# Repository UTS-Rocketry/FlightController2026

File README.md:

# ODIN - UTS Rocketry – Flight Controller 2026

## Version 1.0 - First Flight Test Release

Primary avionics flight controller for the 2026 AURC rocket.

ODIN is a 3.3V STM32-based embedded flight controller designed to manage flight-state detection, onboard sensor acquisition, telemetry transmission, and flight data logging. This release represents the first hardware-and-firmware test release for an upcoming flight test.

The current firmware is intentionally simple and robust. It runs on a superloop architecture without DMA and uses a watchdog for fault recovery. The system has been tested using hardware-in-the-loop simulated flight data and has operated reliably during testing.

---

## System Overview

### Microcontroller

* STM32 F4-series microcontroller
* 3.3V logic domain
* SWD programming and debugging via ST-Link
* Optional USB device support planned for future debug and firmware workflows
* Hardware timers available for deterministic event timing
* Watchdog enabled for fault recovery

---

## Current Firmware Architecture

The first flight test firmware uses a simple superloop design.

### Current Implementation

* No RTOS
* No DMA
* Polling-based peripheral handling
* Watchdog-supervised main loop
* Deterministic flight-state logic
* Sensor sampling over shared SPI bus
* Flash-based data logging
* LoRa telemetry transmission
* Hardware-in-the-loop test data support

This architecture was selected for the first test release to reduce complexity and improve reliability during initial flight testing.

---

## Sensors

All primary sensors are currently connected on a shared SPI bus.

### Barometer

* SPI pressure sensor
* Used for altitude estimation
* Used for flight-state detection and validation
* Locally decoupled according to sensor requirements

### IMU

* SPI accelerometer and gyroscope
* Used for:

  * Boost detection
  * Apogee validation
  * Motion and orientation monitoring
* Interrupt-capable lines available for future firmware revisions

### GPS

GPS support is planned for ODIN but is not included in the current first-flight test release due to hardware issues.

Planned GPS functions include:

* Real-time position tracking
* Post-flight recovery support
* Telemetry downlink of GPS coordinates
* Position logging to onboard storage

---

## Telemetry - SX1262 LoRa

ODIN uses an SX1262-based LoRa radio for long-range telemetry transmission.

### Current Telemetry Features

* LoRa telemetry transmission enabled
* Flight-state downlink
* Sensor-derived flight data downlink
* Battery voltage downlink
* Packet scheduling is handled in the main superloop

### Planned / Future Telemetry Features

* GPS coordinate transmission
* More complete telemetry packet structure
* Configurable LoRa parameters
* Improved fault handling for radio errors

---

## Data Logging

### Current Storage

The current first flight test release uses onboard flash memory as the primary data storage medium.

Flash logging is used because the microSD card interface was dropped from the current release after wiring issues were found during testing.

### microSD Status

microSD logging was planned for this revision; however, the SD card wiring was incorrect, and the SD card interface is not used in this test release.

### Logged / Stored Parameters

The current firmware is intended to store key flight data, including:

* Timestamp or sample counter
* Raw pressure
* Calculated altitude
* IMU acceleration
* IMU gyroscope data
* Flight-state transitions
* Battery voltage
* Event flags

---

## Power Architecture

* Main system input rail
* 3.3V regulated logic rail
* ADC-based battery voltage monitoring through resistor divider
* Local decoupling at each IC
* Bulk capacitance near high-current and noise-sensitive devices
* Solid ground reference for digital logic and sensors

### Design Considerations

* All digital logic operates at 3.3V
* Shared SPI bus used for sensors and peripherals
* Short SPI traces where possible
* Source termination is considered for high-speed SPI lines
* Switching regulator noise kept away from sensitive sensor and RF sections
* Ground reference continuity is maintained across the board

---

## Programming & Debugging

### SWD Interface

SWD is the primary programming and debugging interface.

Signals:

* SWDIO
* SWCLK
* GND
* 3.3V reference
* NRST

Used for:

* Firmware flashing
* Breakpoint debugging
* Register inspection
* Fault investigation

### USB

USB support is optional and planned for future development.

Potential future uses:

* CDC virtual COM port for debug output
* DFU firmware update support
* Ground-test data streaming

---

## First Flight Test Release Notes

This release is prepared for the first ODIN flight test.

### Included

* STM32-based flight controller firmware
* Superloop firmware architecture
* Watchdog fault recovery
* SPI sensor acquisition
* Barometer-based altitude estimation
* IMU data acquisition
* LoRa telemetry transmission
* Flash-based data logging
* Battery voltage monitoring
* Hardware-in-the-loop simulated flight data testing

### Not Included in This Release

* GPS support
* microSD card logging
* DMA-based peripheral handling
* RTOS task scheduling
* Full sensor-fusion stack
* Final telemetry packet format
* Final competition firmware architecture

### Known Issues

* The microSD card interface is not used due to incorrect wiring
* GPS is not included in this release due to hardware issues
* Firmware currently uses polling rather than DMA
* Current release prioritises reliability and simplicity over final feature completeness

---

## Core Features

* Sensor initialisation and health checks
* Watchdog-supervised main loop
* Deterministic flight-state transitions
* Flash-based onboard data storage
* LoRa telemetry transmission
* Battery voltage monitoring
* Brownout and fault-awareness support
* Hardware-in-the-loop simulation data testing

---

## Development Roadmap

Future firmware and hardware revisions are expected to include:

* GPS integration
* Corrected microSD card interface
* Improved onboard logging backend
* DMA support for selected peripherals
* More complete sensor fusion
* Refined telemetry packet scheduling
* Expanded fault detection and recovery
* USB debug and DFU support
* Full competition-ready flight software

---

## Contributors
* Michael Basangan: Software Lead
* Aditya Sriram: Advisor

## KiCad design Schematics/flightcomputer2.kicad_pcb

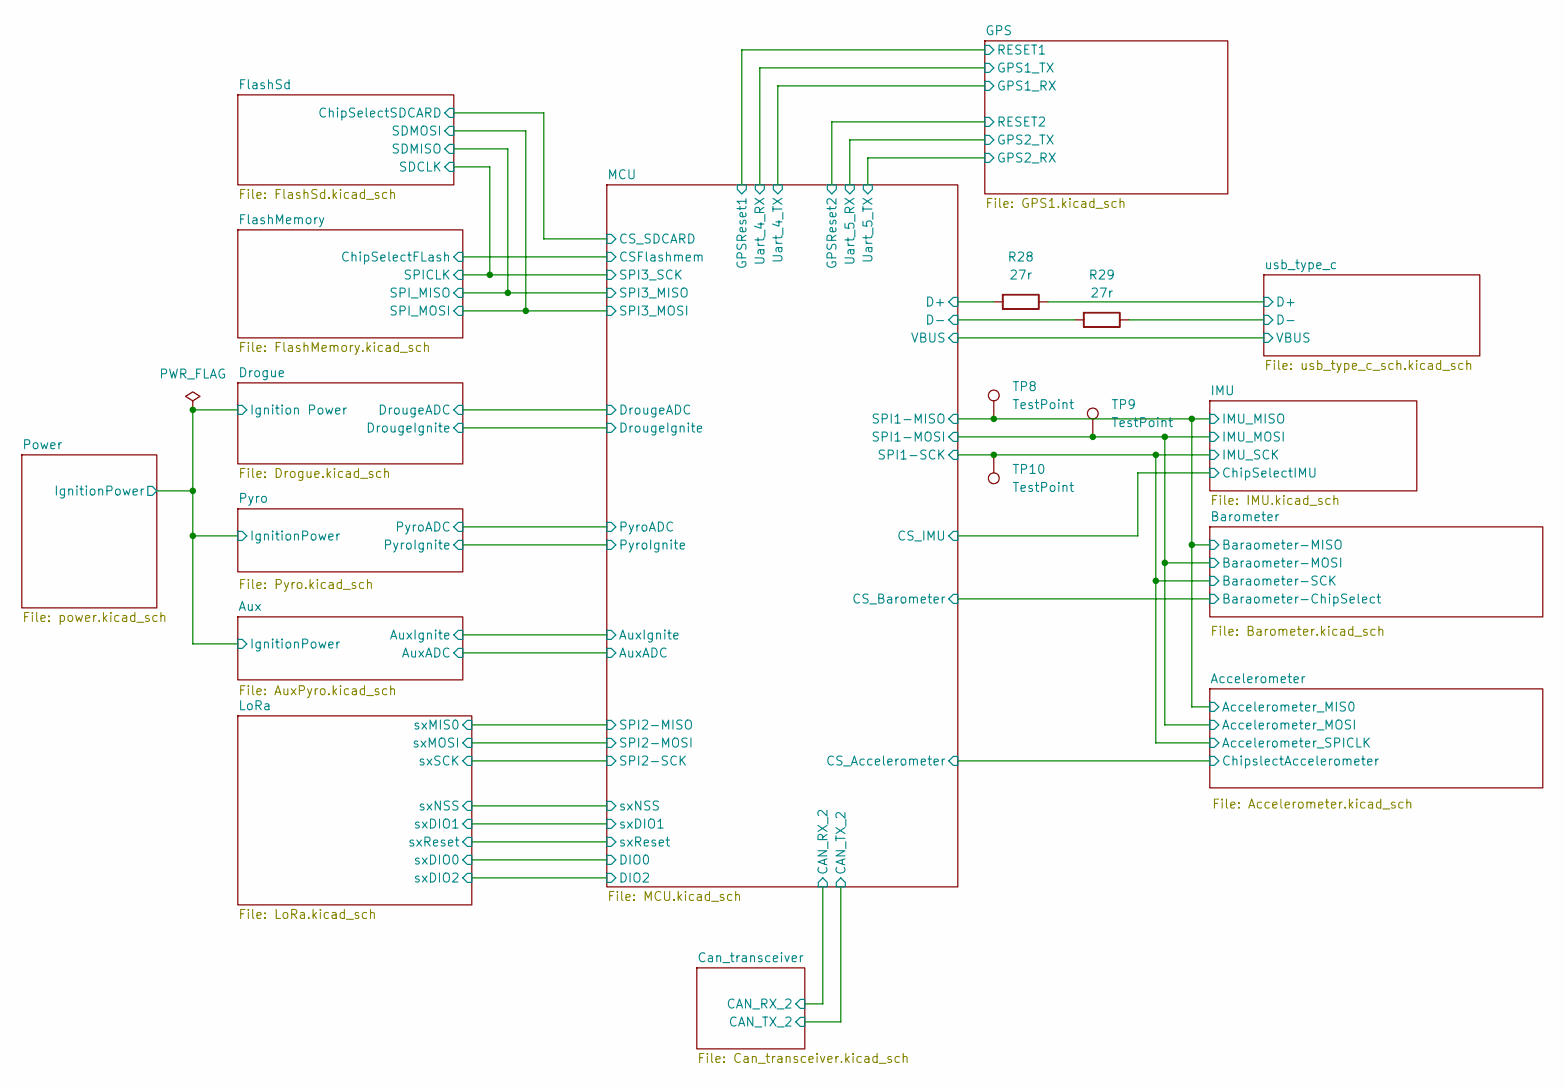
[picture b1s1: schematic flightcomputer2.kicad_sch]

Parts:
R28, R29: 27r; R_0805_2012Metric_Pad1.20x1.40mm_HandSolder; LCSC C17594
TP8, TP9, TP10: TestPoint; TestPoint_Pad_1.5x1.5mm

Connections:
/Accelerometer/Accelerometer_MIS0: TP8.1 (1_1); also elsewhere on the board
/Accelerometer/Accelerometer_MOSI: TP9.1 (1_1); also elsewhere on the board
/Accelerometer/Accelerometer_SPICLK: TP10.1 (1_1); also elsewhere on the board
/MCU/D+: R28.2; also elsewhere on the board
/MCU/D-: R29.2; also elsewhere on the board
/usb_type_c/D+: R28.1; also elsewhere on the board
/usb_type_c/D-: R29.1; also elsewhere on the board

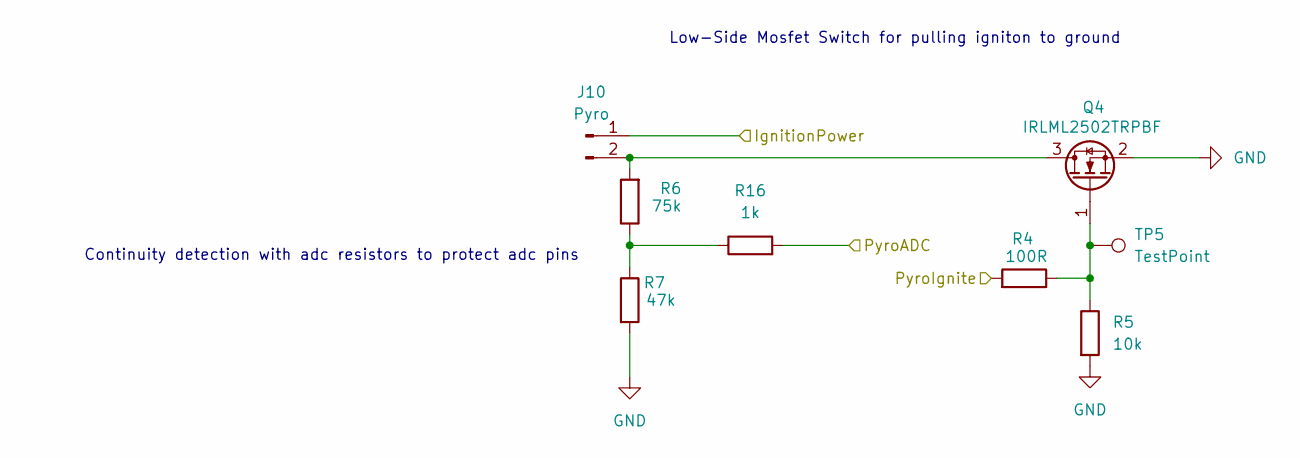
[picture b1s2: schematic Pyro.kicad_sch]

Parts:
J10: Pyro; MOLEX_26013114; LCSC C17644051
Q4: IRLML2502TRPBF; SOT23; LCSC C2589
R4: 100R; R_0805_2012Metric_Pad1.20x1.40mm_HandSolder; LCSC C17408
R5: 10k; R_0805_2012Metric_Pad1.20x1.40mm_HandSolder; LCSC C17414
R6: 75k; R_0805_2012Metric_Pad1.20x1.40mm_HandSolder; LCSC C17819
R7: 47k; R_0805_2012Metric_Pad1.20x1.40mm_HandSolder; LCSC C17713
R16: 1k; R_0805_2012Metric_Pad1.20x1.40mm_HandSolder; LCSC C17513
TP5: TestPoint; TestPoint_Pad_1.5x1.5mm

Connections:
/Aux/IgnitionPower: J10.1; also elsewhere on the board
/MCU/PyroADC: R16.2; also elsewhere on the board
/MCU/PyroIgnite: R4.2; also elsewhere on the board
GND: Q4.2 (S), R5.2, R7.2; also elsewhere on the board
unnamed: J10.2, Q4.3 (D), R6.2
unnamed: Q4.1 (G), R4.1, R5.1, TP5.1 (1_1)
unnamed: R6.1, R7.1, R16.1

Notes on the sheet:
Low-Side Mosfet Switch for pulling igniton to ground
Continuity detection with adc resistors to protect adc pins

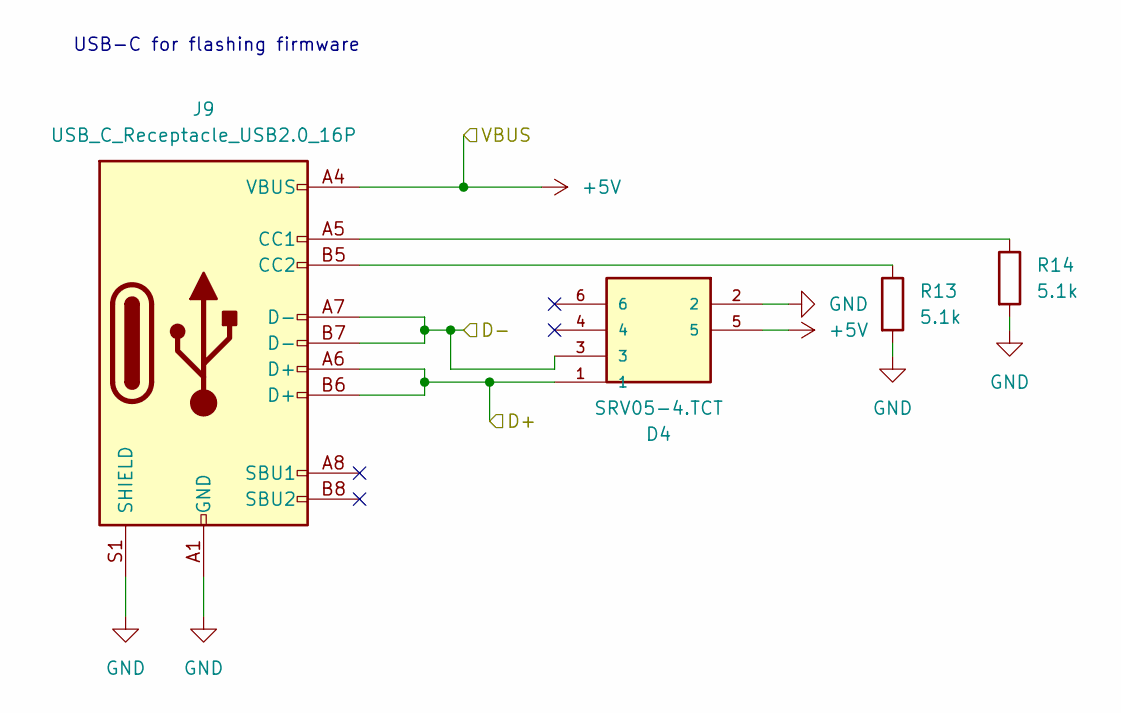
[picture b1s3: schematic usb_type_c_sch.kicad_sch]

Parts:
D4: SRV05-4.TCT; SOT95P280X145-6N; MANUFACTURER_PART_NUMBER SRV05-4.TCT; LCSC C13612
J9: USB_C_Receptacle_USB2.0_16P; USB_C_Receptacle_HRO_TYPE-C-31-M-12; LCSC C165948
R13, R14: 5.1k; R_0805_2012Metric_Pad1.20x1.40mm_HandSolder; LCSC C27834

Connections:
+5V: D4.5, J9.A4 (VBUS), J9.A9 (VBUS), J9.B4 (VBUS), J9.B9 (VBUS); also elsewhere on the board
/usb_type_c/D+: D4.1, J9.A6 (D+), J9.B6 (D+); also elsewhere on the board
/usb_type_c/D-: D4.3, J9.A7 (D-), J9.B7 (D-); also elsewhere on the board
GND: D4.2, J9.A1 (GND), J9.A12 (GND), J9.B1 (GND), J9.B12 (GND), J9.S1 (SHIELD), R13.2, R14.2; also elsewhere on the board
unnamed: J9.A5 (CC1), R14.1
unnamed: J9.B5 (CC2), R13.1

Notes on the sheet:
USB-C for flashing firmware

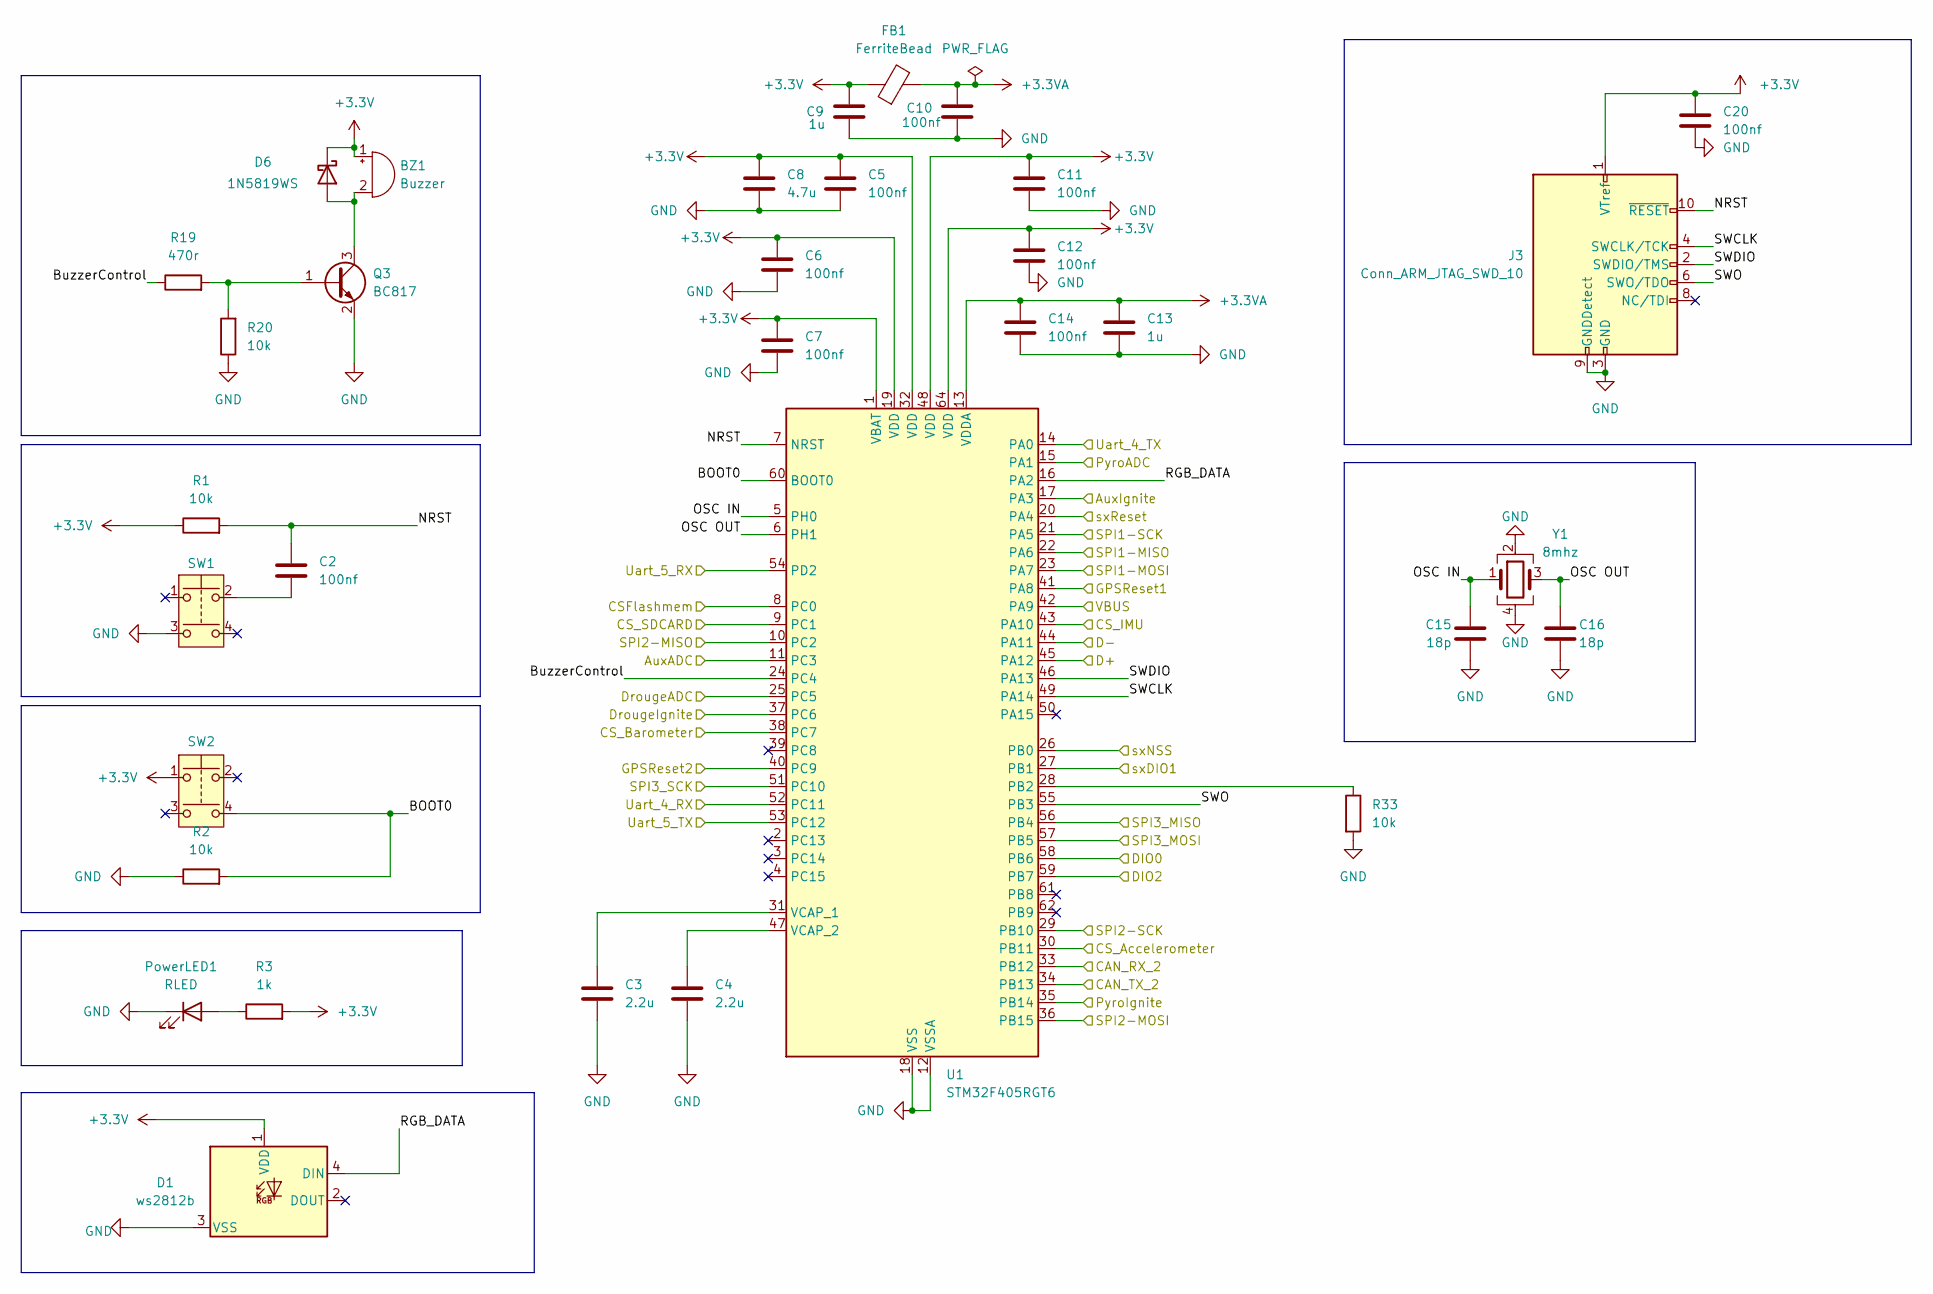
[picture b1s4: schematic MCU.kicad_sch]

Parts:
BZ1: Buzzer; Buzzer_12x9.5RM7.6; LCSC C96093
C2, C5, C6, C7, C10, C11, C12, C14, C20: 100nf; C_0805_2012Metric_Pad1.18x1.45mm_HandSolder; LCSC C49678
C3, C4: 2.2u; C_0805_2012Metric_Pad1.18x1.45mm_HandSolder; LCSC C377773
C8: 4.7u; C_0805_2012Metric_Pad1.18x1.45mm_HandSolder; LCSC C1779
C9, C13: 1u; C_0805_2012Metric_Pad1.18x1.45mm_HandSolder; LCSC C28323
C15, C16: 18p; C_0805_2012Metric_Pad1.18x1.45mm_HandSolder; LCSC C113825
D1: ws2812b; LED_WS2812B_PLCC4_5.0x5.0mm_P3.2mm; LCSC C2761795
D6: 1N5819WS; D_SOD-323; LCSC C191023
FB1: FerriteBead; R_0805_2012Metric_Pad1.20x1.40mm_HandSolder; LCSC C1015
J3: Conn_ARM_JTAG_SWD_10; PinHeader_2x05_P1.27mm_Vertical; LCSC C22438120
PowerLED1: RLED; LED_0603_1608Metric_Pad1.05x0.95mm_HandSolder; LCSC C965799
Q3: BC817; SOT-23; LCSC C39828
R1, R2, R20: 10k; R_0805_2012Metric_Pad1.20x1.40mm_HandSolder; LCSC C17414
R3: 1k; R_0805_2012Metric_Pad1.20x1.40mm_HandSolder; LCSC C17513
R19: 470r; R_0805_2012Metric_Pad1.20x1.40mm_HandSolder; LCSC C17710
R33: 10k; R_0805_2012Metric; LCSC C17414
SW1, SW2: SAMZO G4R0015010; LCSC C49393646
U1: STM32F405RGT6; LQFP-64_10x10mm_P0.5mm; LCSC C15742
Y1: 8mhz; Crystal_SMD_3225-4Pin_3.2x2.5mm_HandSoldering; LCSC C19723344

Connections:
+3.3V: BZ1.1 (+), C5.1, C6.1, C7.1, C8.1, C9.2, C11.1, C12.1, C20.1, D1.1 (VDD), D6.1 (K), FB1.1, J3.1 (VTref), R1.1, R3.2, SW2.1, U1.1 (VBAT), U1.19 (VDD), U1.32 (VDD), U1.48 (VDD), U1.64 (VDD); also elsewhere on the board
+3.3VA: C10.2, C13.1, C14.1, FB1.2, U1.13 (VDDA)
+5V: U1.42 (PA9); also elsewhere on the board
/Accelerometer/Accelerometer_MIS0: U1.22 (PA6); also elsewhere on the board
/Accelerometer/Accelerometer_MOSI: U1.23 (PA7); also elsewhere on the board
/Accelerometer/Accelerometer_SPICLK: U1.21 (PA5); also elsewhere on the board
/Accelerometer/ChipslectAccelerometer: U1.30 (PB11); also elsewhere on the board
/Aux/AuxADC: U1.11 (PC3); also elsewhere on the board
/Aux/AuxIgnite: U1.17 (PA3); also elsewhere on the board
/Barometer/Baraometer-ChipSelect: U1.38 (PC7); also elsewhere on the board
/Can_transceiver/CAN_RX_2: U1.33 (PB12); also elsewhere on the board
/Can_transceiver/CAN_TX_2: U1.34 (PB13); also elsewhere on the board
/Drogue/DrougeADC: U1.25 (PC5); also elsewhere on the board
/Drogue/DrougeIgnite: U1.37 (PC6); also elsewhere on the board
/FlashMemory/ChipSelectFLash: U1.8 (PC0); also elsewhere on the board
/FlashMemory/SPICLK: U1.51 (PC10); also elsewhere on the board
/FlashMemory/SPI_MISO: U1.56 (PB4); also elsewhere on the board
/FlashMemory/SPI_MOSI: U1.57 (PB5); also elsewhere on the board
/FlashSd/ChipSelectSDCARD: U1.9 (PC1); also elsewhere on the board
/GPS/GPS1_RX: U1.14 (PA0); also elsewhere on the board
/GPS/GPS1_TX: U1.52 (PC11); also elsewhere on the board
/GPS/GPS2_RX: U1.53 (PC12); also elsewhere on the board
/GPS/GPS2_TX: U1.54 (PD2); also elsewhere on the board
/GPS/RESET1: U1.41 (PA8); also elsewhere on the board
/GPS/RESET2: U1.40 (PC9); also elsewhere on the board
/IMU/ChipSelectIMU: U1.43 (PA10); also elsewhere on the board
/LoRa/sxDIO0: U1.58 (PB6); also elsewhere on the board
/LoRa/sxDIO1: U1.27 (PB1); also elsewhere on the board
/LoRa/sxDIO2: U1.59 (PB7); also elsewhere on the board
/LoRa/sxMIS0: U1.10 (PC2); also elsewhere on the board
/LoRa/sxMOSI: U1.36 (PB15); also elsewhere on the board
/LoRa/sxNSS: U1.26 (PB0); also elsewhere on the board
/LoRa/sxReset: U1.20 (PA4); also elsewhere on the board
/LoRa/sxSCK: U1.29 (PB10); also elsewhere on the board
/MCU/BOOT0: R2.2, SW2.4, U1.60 (BOOT0)
/MCU/BuzzerControl: R19.1, U1.24 (PC4)
/MCU/D+: U1.45 (PA12); also elsewhere on the board
/MCU/D-: U1.44 (PA11); also elsewhere on the board
/MCU/NRST: C2.1, J3.10 (~RESET), R1.2, U1.7 (NRST)
/MCU/OSC IN: C15.1, U1.5 (PH0), Y1.1
/MCU/OSC OUT: C16.1, U1.6 (PH1), Y1.3
/MCU/PyroADC: U1.15 (PA1); also elsewhere on the board
/MCU/PyroIgnite: U1.35 (PB14); also elsewhere on the board
/MCU/RGB_DATA: D1.4 (DIN), U1.16 (PA2)
/MCU/SWCLK: J3.4 (SWCLK/TCK), U1.49 (PA14)
/MCU/SWDIO: J3.2 (SWDIO/TMS), U1.46 (PA13)
/MCU/SWO: J3.6 (SWO/TDO), U1.55 (PB3)
GND: C3.2, C4.2, C5.2, C6.2, C7.2, C8.2, C9.1, C10.1, C11.2, C12.2, C13.2, C14.2, C15.2, C16.2, C20.2, D1.3 (VSS), J3.3 (GND), J3.5 (GND), J3.9 (GNDDetect), PowerLED1.1 (K), Q3.2 (E), R2.1, R20.1, R33.2, SW1.3, U1.12 (VSSA), U1.18 (VSS), U1.63 (VSS), Y1.2, Y1.4; also elsewhere on the board
unnamed: BZ1.2 (-), D6.2 (A), Q3.3 (C)
unnamed: C2.2, SW1.2
unnamed: PowerLED1.2 (A), R3.1
unnamed: Q3.1 (B), R19.2, R20.2
unnamed: R33.1, U1.28 (PB2)
unnamed: C3.1, U1.31 (VCAP_1)
unnamed: C4.1, U1.47 (VCAP_2)

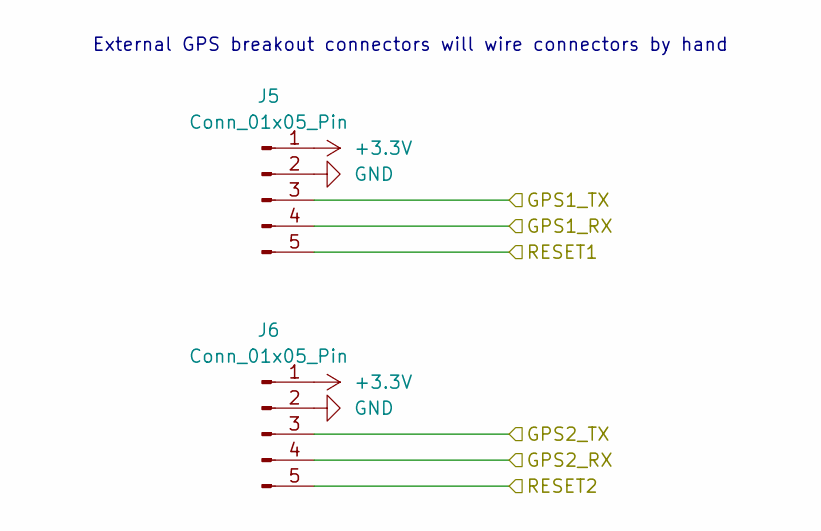
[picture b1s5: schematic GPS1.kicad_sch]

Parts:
J5, J6: Conn_01x05_Pin; JST_B5B-XH-A; LCSC C157991

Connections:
+3.3V: J5.1, J6.1; also elsewhere on the board
/GPS/GPS1_RX: J5.4; also elsewhere on the board
/GPS/GPS1_TX: J5.3; also elsewhere on the board
/GPS/GPS2_RX: J6.4; also elsewhere on the board
/GPS/GPS2_TX: J6.3; also elsewhere on the board
/GPS/RESET1: J5.5; also elsewhere on the board
/GPS/RESET2: J6.5; also elsewhere on the board
GND: J5.2, J6.2; also elsewhere on the board

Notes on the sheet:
External GPS breakout connectors will wire connectors by hand

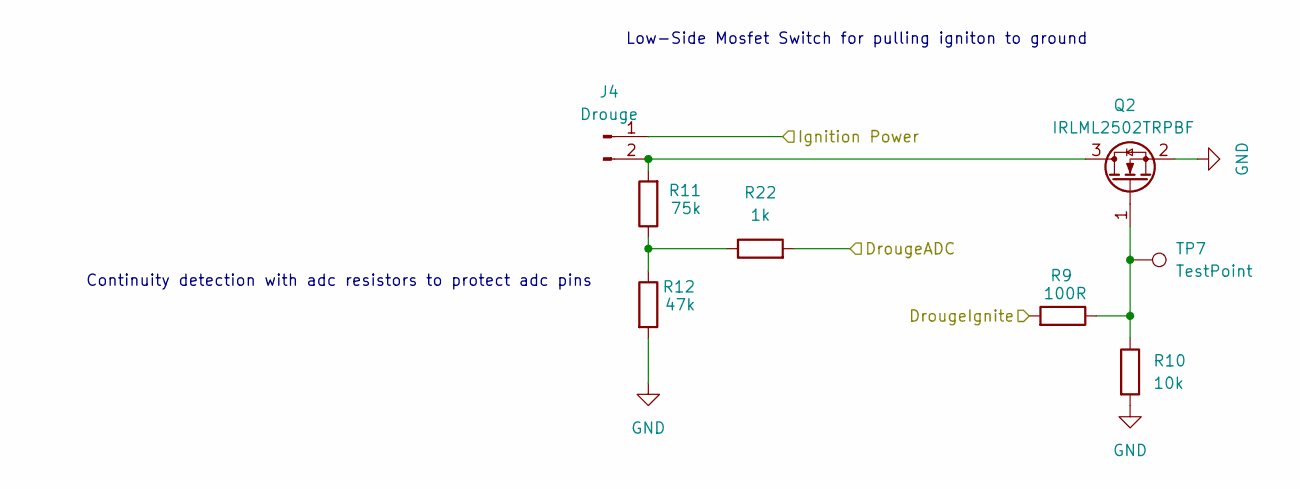
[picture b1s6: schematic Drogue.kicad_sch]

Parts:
J4: Drouge; MOLEX_26013114; LCSC C17644051
Q2: IRLML2502TRPBF; SOT23; LCSC C2589
R9: 100R; R_0805_2012Metric_Pad1.20x1.40mm_HandSolder; LCSC C17408
R10: 10k; R_0805_2012Metric_Pad1.20x1.40mm_HandSolder; LCSC C17414
R11: 75k; R_0805_2012Metric_Pad1.20x1.40mm_HandSolder; LCSC C17819
R12: 47k; R_0805_2012Metric_Pad1.20x1.40mm_HandSolder; LCSC C17713
R22: 1k; R_0805_2012Metric_Pad1.20x1.40mm_HandSolder; LCSC C17513
TP7: TestPoint; TestPoint_Pad_1.5x1.5mm

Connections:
/Aux/IgnitionPower: J4.1; also elsewhere on the board
/Drogue/DrougeADC: R22.2; also elsewhere on the board
/Drogue/DrougeIgnite: R9.2; also elsewhere on the board
GND: Q2.2 (S), R10.2, R12.2; also elsewhere on the board
unnamed: J4.2, Q2.3 (D), R11.2
unnamed: Q2.1 (G), R9.1, R10.1, TP7.1 (1_1)
unnamed: R11.1, R12.1, R22.1

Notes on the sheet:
Continuity detection with adc resistors to protect adc pins
Low-Side Mosfet Switch for pulling igniton to ground

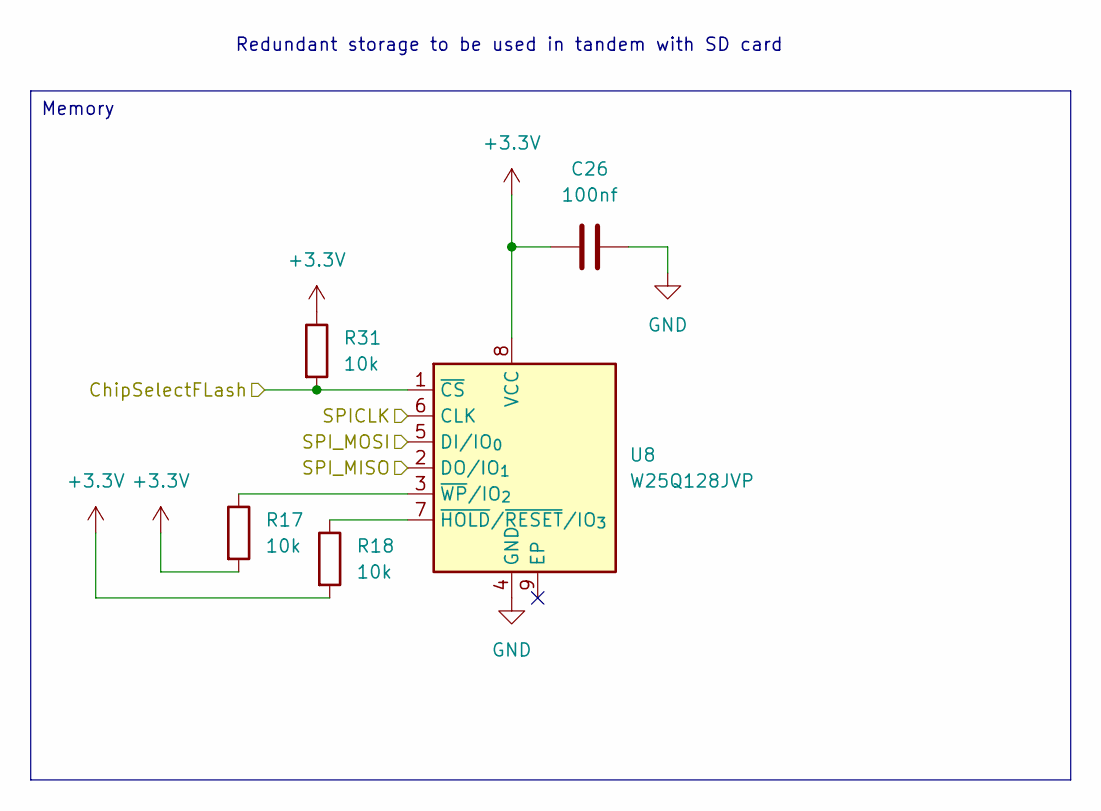
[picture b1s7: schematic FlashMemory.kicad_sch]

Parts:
C26: 100nf; C_0805_2012Metric_Pad1.18x1.45mm_HandSolder; LCSC C49678
R17, R18, R31: 10k; R_0805_2012Metric_Pad1.20x1.40mm_HandSolder; LCSC C17414
U8: W25Q128JVP; WSON-8-1EP_6x5mm_P1.27mm_EP3.4x4.3mm; LCSC C190862

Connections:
+3.3V: C26.1, R17.2, R18.2, R31.1, U8.8 (VCC); also elsewhere on the board
/FlashMemory/ChipSelectFLash: R31.2, U8.1 (~CS); also elsewhere on the board
/FlashMemory/SPICLK: U8.6 (CLK); also elsewhere on the board
/FlashMemory/SPI_MISO: U8.2 (DO/IO_{1}); also elsewhere on the board
/FlashMemory/SPI_MOSI: U8.5 (DI/IO_{0}); also elsewhere on the board
GND: C26.2, U8.4 (GND); also elsewhere on the board
unnamed: R18.1, U8.7 (~HOLD/~RESET/IO_{3})
unnamed: R17.1, U8.3 (~WP/IO_{2})

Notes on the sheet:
Redundant storage to be used in tandem with SD card
Memory

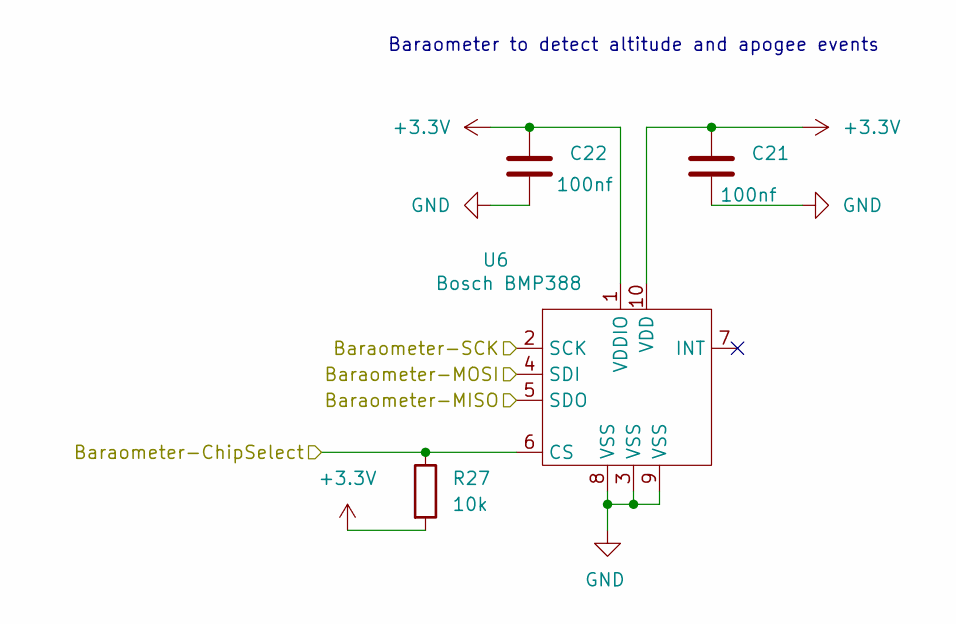
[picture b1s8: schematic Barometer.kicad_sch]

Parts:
C21, C22: 100nf; C_0805_2012Metric_Pad1.18x1.45mm_HandSolder; LCSC C49678
R27: 10k; R_0805_2012Metric_Pad1.20x1.40mm_HandSolder; LCSC C17414
U6: Bosch BMP388; PQFN50P200X200X80-10N; LCSC C779278

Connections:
+3.3V: C21.1, C22.1, R27.2, U6.1 (VDDIO), U6.10 (VDD); also elsewhere on the board
/Accelerometer/Accelerometer_MIS0: U6.5 (SDO); also elsewhere on the board
/Accelerometer/Accelerometer_MOSI: U6.4 (SDI); also elsewhere on the board
/Accelerometer/Accelerometer_SPICLK: U6.2 (SCK); also elsewhere on the board
/Barometer/Baraometer-ChipSelect: R27.1, U6.6 (CS); also elsewhere on the board
GND: C21.2, C22.2, U6.3 (VSS), U6.8 (VSS), U6.9 (VSS); also elsewhere on the board

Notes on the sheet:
Baraometer to detect altitude and apogee events

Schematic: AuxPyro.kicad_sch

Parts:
J2: Pyro; MOLEX_26013114; LCSC C17644051
Q1: IRLML2502TRPBF; SOT23; LCSC C2589
R21: 1k; R_0805_2012Metric_Pad1.20x1.40mm_HandSolder; LCSC C17513
R23: 100R; R_0805_2012Metric_Pad1.20x1.40mm_HandSolder; LCSC C17408
R24: 10k; R_0805_2012Metric_Pad1.20x1.40mm_HandSolder; LCSC C17414
R25: 75k; R_0805_2012Metric_Pad1.20x1.40mm_HandSolder; LCSC C17819
R26: 47k; R_0805_2012Metric_Pad1.20x1.40mm_HandSolder; LCSC C17713
TP6: TestPoint; TestPoint_Pad_1.5x1.5mm

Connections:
/Aux/AuxADC: R21.2; also elsewhere on the board
/Aux/AuxIgnite: R23.2; also elsewhere on the board
/Aux/IgnitionPower: J2.1; also elsewhere on the board
GND: Q1.2 (S), R24.2, R26.2; also elsewhere on the board
unnamed: J2.2, Q1.3 (D), R25.2
unnamed: Q1.1 (G), R23.1, R24.1, TP6.1 (1_1)
unnamed: R21.1, R25.1, R26.1

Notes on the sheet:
Continuity detection with adc resistors to protect adc pins
Low-Side Mosfet Switch for pulling igniton to ground

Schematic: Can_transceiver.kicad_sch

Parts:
C17: 100nf; C_0805_2012Metric_Pad1.18x1.45mm_HandSolder; LCSC C49678
CAN_IN1: CAN; MOLEX_26013114; LCSC C17644051
CAN_OUT1: CAN; MOLEX_26013114; LCSC C17644051
JP1: SolderJumper_2_Open; SolderJumper-2_P1.3mm_Open_TrianglePad1.0x1.5mm; not fitted
R8: 120R; R_0805_2012Metric_Pad1.20x1.40mm_HandSolder; LCSC C17437
U2: SN65HVD230; SOIC-8_3.9x4.9mm_P1.27mm; LCSC C12084

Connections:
+3.3V: C17.1, U2.3 (VCC); also elsewhere on the board
/Can_transceiver/CANH: CAN_IN1.1, CAN_OUT1.1, R8.1, U2.7 (CANH)
/Can_transceiver/CANL: CAN_IN1.2, CAN_OUT1.2, JP1.2 (B), U2.6 (CANL)
/Can_transceiver/CAN_RX_2: U2.4 (R); also elsewhere on the board
/Can_transceiver/CAN_TX_2: U2.1 (D); also elsewhere on the board
GND: C17.2, U2.2 (GND), U2.8 (Rs); also elsewhere on the board
unnamed: JP1.1 (A), R8.2

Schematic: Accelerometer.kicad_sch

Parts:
C27: 100nf; C_0805_2012Metric_Pad1.18x1.45mm_HandSolder; LCSC C49678
C28: 1u; C_0805_2012Metric_Pad1.18x1.45mm_HandSolder; LCSC C28323
R32: 10k; R_0805_2012Metric_Pad1.20x1.40mm_HandSolder; LCSC C17414
U9: H3LIS331DL; PQFN50P300X300X100-16N; LCSC C2655074

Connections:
+3.3V: C27.2, C28.2, R32.1, U9.1 (Vdd_IO), U9.14 (VDD), U9.15 (VDD); also elsewhere on the board
/Accelerometer/Accelerometer_MIS0: U9.7 (SDO/SA0); also elsewhere on the board
/Accelerometer/Accelerometer_MOSI: U9.6 (SDA/SDI/SDO); also elsewhere on the board
/Accelerometer/Accelerometer_SPICLK: U9.4 (SCL/SPC); also elsewhere on the board
/Accelerometer/ChipslectAccelerometer: R32.2, U9.8 (CS); also elsewhere on the board
GND: C27.1, C28.1, U9.5 (GND), U9.12 (GND); also elsewhere on the board

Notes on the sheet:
High g imu for liftoff data

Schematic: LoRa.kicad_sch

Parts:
C1: 100nf; C_0805_2012Metric_Pad1.18x1.45mm_HandSolder; LCSC C49678
J7: Conn_Coaxial_Small; SMA_Amphenol_132291_Vertical; LCSC C3172376
U5: RFM95W-915S2; XCVR_RFM95W-915S2; LCSC C2844473

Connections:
+3.3V: C1.1, U5.13 (3.3V); also elsewhere on the board
/LoRa/sxDIO0: U5.14 (DIO0); also elsewhere on the board
/LoRa/sxDIO1: U5.15 (DIO1); also elsewhere on the board
/LoRa/sxDIO2: U5.16 (DIO2); also elsewhere on the board
/LoRa/sxMIS0: U5.2 (MISO); also elsewhere on the board
/LoRa/sxMOSI: U5.3 (MOSI); also elsewhere on the board
/LoRa/sxNSS: U5.5 (NSS); also elsewhere on the board
/LoRa/sxReset: U5.6 (RESET); also elsewhere on the board
/LoRa/sxSCK: U5.4 (SCK); also elsewhere on the board
GND: C1.2, J7.2 (Ext), U5.1 (GND), U5.8 (GND), U5.10 (GND); also elsewhere on the board
unnamed: J7.1 (In), U5.9 (ANT)

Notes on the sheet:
Lora module to coaxial connector

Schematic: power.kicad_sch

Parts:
C18: 100nf; C_0805_2012Metric_Pad1.18x1.45mm_HandSolder; LCSC C49678
C19: 10u; C_0805_2012Metric_Pad1.18x1.45mm_HandSolder; LCSC C15850
D2, D3: D_Schottky; D_2114_3652Metric; LCSC C113936
Q6: Q_PMOS_GSD; SOIC127P599X175-8N; LCSC C16072
R30: 47k; R_0805_2012Metric_Pad1.20x1.40mm_HandSolder; LCSC C17713
TP1, TP2, TP3: TestPoint; TestPoint_Pad_1.5x1.5mm
TP4: TestPoint; TestPoint_Pad_2.5x2.5mm
U3: PowerIn; MOLEX_26013114; LCSC C17644051
U4: LDL1117-3.3; SOT230P700X180-4N; LCSC C435835

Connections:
+3.3V: C19.1, TP3.1 (1_1), U4.2 (Vout), U4.4 (Vout); also elsewhere on the board
+5V: D3.2 (A); also elsewhere on the board
+BATT: Q6.1 (S), Q6.2 (Source), Q6.3 (Source), TP1.1 (1_1), U3.1
/Aux/IgnitionPower: D2.2 (A), Q6.5 (D), Q6.6 (Drain), Q6.7 (Drain), TP2.1 (1_1); also elsewhere on the board
GND: C18.2, C19.2, R30.2, TP4.1 (1_1), U3.2, U4.1 (GND); also elsewhere on the board
unnamed: C18.1, D2.1 (K), D3.1 (K), U4.3 (Vin)
unnamed: Q6.4 (G), R30.1

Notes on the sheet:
Flowback protection for usb and battery
The main protection point for the mosfet is the adc continuty checking pins
P-mosfet for reverse polarity protection (be advised extra pins are there just to sync with the footprint but treated as a normal p-mosfet)
Power in connector

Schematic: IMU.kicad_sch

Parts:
C24, C25: 100nf; C_0805_2012Metric_Pad1.18x1.45mm_HandSolder; LCSC C49678
R36: 10k; R_0805_2012Metric_Pad1.20x1.40mm_HandSolder; LCSC C17414
U7: LSM6DS3TR-C; LGA-14-2.5X3MM; LCSC C2655100

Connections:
+3.3V: C24.1, C25.1, R36.1, U7.2 (SDx), U7.3 (SCx), U7.5 (VDDIO), U7.8 (VDD); also elsewhere on the board
/Accelerometer/Accelerometer_MIS0: U7.1 (SDO/SA0); also elsewhere on the board
/Accelerometer/Accelerometer_MOSI: U7.14 (SDA); also elsewhere on the board
/Accelerometer/Accelerometer_SPICLK: U7.13 (SCL); also elsewhere on the board
/IMU/ChipSelectIMU: R36.2, U7.12 (CS); also elsewhere on the board
GND: C24.2, C25.2, U7.6 (GND), U7.7 (GND); also elsewhere on the board

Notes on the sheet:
Imu for control systems and data logging

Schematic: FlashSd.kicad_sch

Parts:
J8: Micro_SD_Card; microSD_HC_Molex_47219-2001; LCSC C164170
R15: 10k; R_0805_2012Metric_Pad1.20x1.40mm_HandSolder; LCSC C17414

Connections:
+3.3V: J8.4 (VDD), R15.1; also elsewhere on the board
/FlashMemory/SPICLK: J8.5 (CLK); also elsewhere on the board
/FlashMemory/SPI_MISO: J8.7 (DAT0); also elsewhere on the board
/FlashMemory/SPI_MOSI: J8.3 (CMD); also elsewhere on the board
/FlashSd/ChipSelectSDCARD: J8.2 (DAT3/CD), R15.2; also elsewhere on the board
GND: J8.6 (VSS), J8.9 (SHIELD); also elsewhere on the board

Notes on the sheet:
SD Card for flight telemetry logging and possible lookup tables for control systems

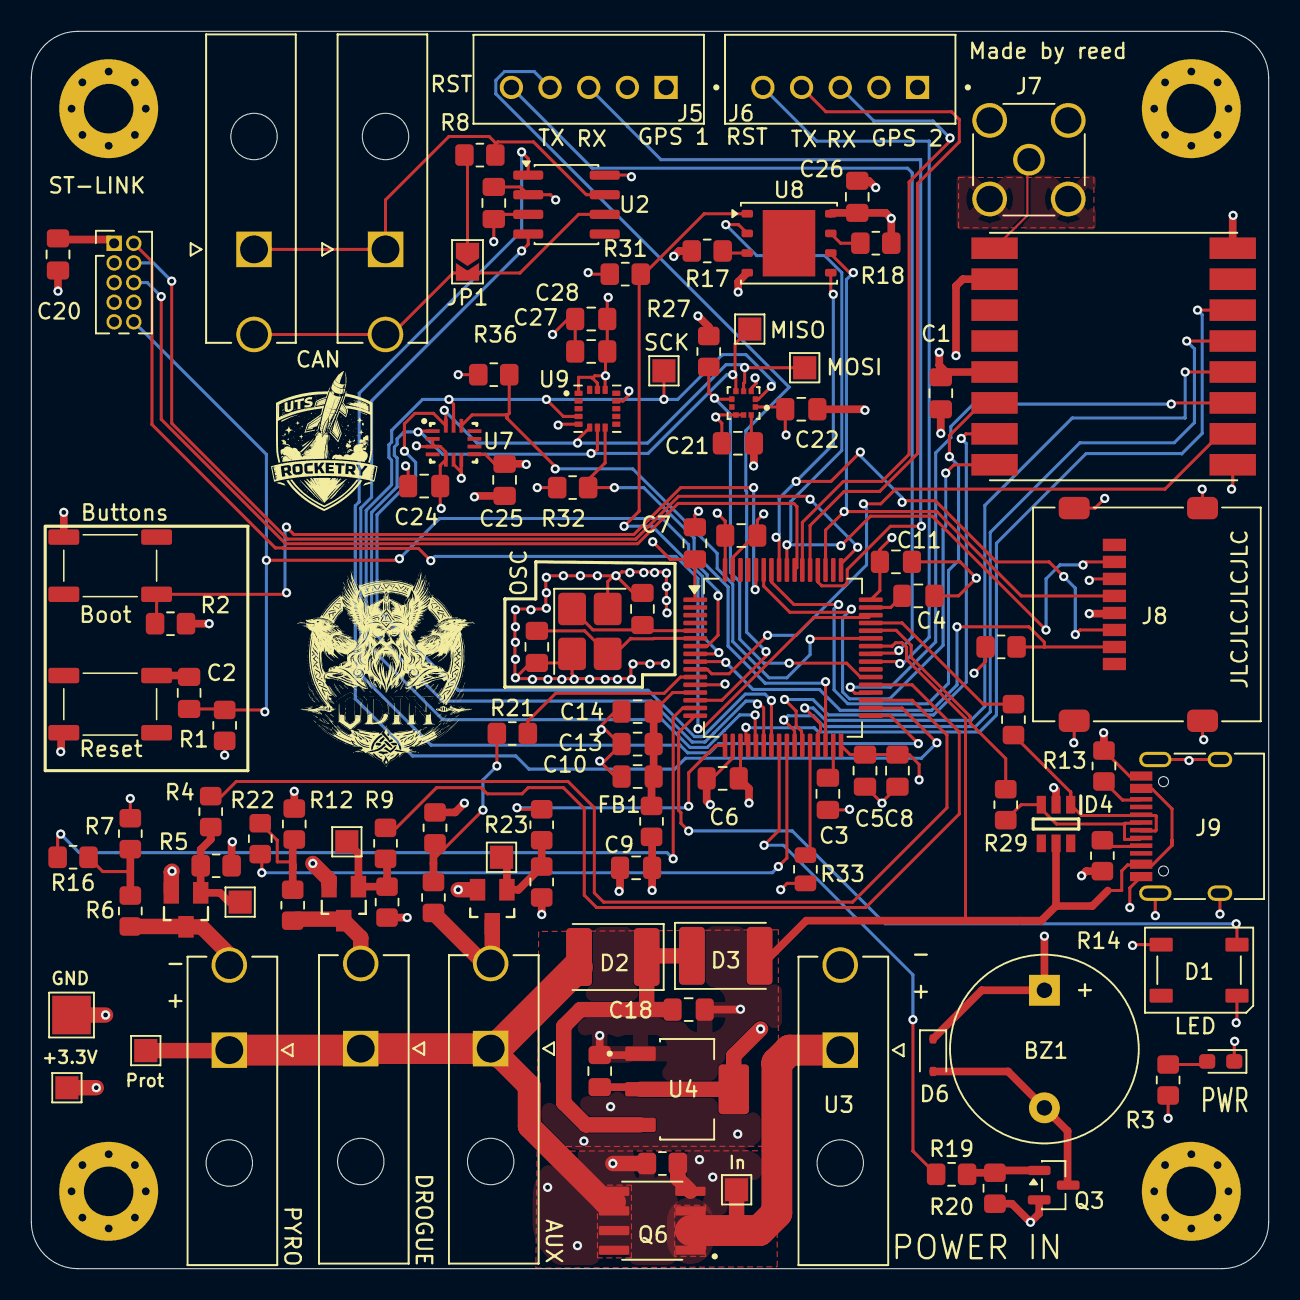
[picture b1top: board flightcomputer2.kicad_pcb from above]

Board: 4 copper layers, 80.0 x 80.0 mm, 108 parts (0 on the bottom side), 78 nets.

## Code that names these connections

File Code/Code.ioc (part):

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Mcu.Name=STM32F405RGTx
Mcu.Package=LQFP64
Mcu.UserName=STM32F405RGTx
PA0-WKUP.Mode=Asynchronous
PA0-WKUP.Signal=UART4_TX
PA1.Signal=ADCx_IN1
PA10.GPIOParameters=PinState,GPIO_Label
PA10.GPIO_Label=CS_IMU
PA10.PinState=GPIO_PIN_SET
PA10.Signal=GPIO_Output
PA11.Mode=Device_Only
PA11.Signal=USB_OTG_FS_DM
PA12.Mode=Device_Only
PA12.Signal=USB_OTG_FS_DP
PA13.Mode=Serial_Wire
PA13.Signal=SYS_JTMS-SWDIO
PA14.Mode=Serial_Wire
PA14.Signal=SYS_JTCK-SWCLK
PA2.GPIOParameters=GPIO_Label
PA2.GPIO_Label=RGBLEDControl
PA2.Signal=S_TIM2_CH3
PA3.GPIOParameters=GPIO_Label
PA3.GPIO_Label=AuxIgnite
PA3.Signal=GPIO_Output
PA5.Mode=Full_Duplex_Master
PA5.Signal=SPI1_SCK
PA6.Mode=Full_Duplex_Master
PA6.Signal=SPI1_MISO
PA7.Mode=Full_Duplex_Master
PA7.Signal=SPI1_MOSI
PA8.GPIOParameters=GPIO_Label
PA8.GPIO_Label=GPS1ResetPin
PA8.Signal=GPIO_Output
PA9.Mode=Activate_VBUS
PA9.Signal=USB_OTG_FS_VBUS
PB0.GPIOParameters=PinState,GPIO_Label
PB0.GPIO_Label=LoRaNssPin
PB0.PinState=GPIO_PIN_SET
PB0.Signal=GPIO_Output
PB1.GPIOParameters=GPIO_Label
PB1.GPIO_Label=LoRaDIO1
PB1.Signal=GPIO_Input
PB10.Mode=Full_Duplex_Master
PB10.Signal=SPI2_SCK
PB11.GPIOParameters=PinState,GPIO_Label
PB11.GPIO_Label=CSAccelerometer
PB11.PinState=GPIO_PIN_SET
PB11.Signal=GPIO_Output
PB12.Mode=CAN_Activate
PB12.Signal=CAN2_RX
PB13.Mode=CAN_Activate
PB13.Signal=CAN2_TX
PB14.GPIOParameters=GPIO_Label
PB14.GPIO_Label=PyroIgnite
PB14.Signal=GPIO_Output
PB15.Mode=Full_Duplex_Master
PB15.Signal=SPI2_MOSI
PB2.GPIOParameters=GPIO_Label
PB2.GPIO_Label=LoRaResetPin
PB2.Signal=GPIO_Output
PB3.Signal=SYS_JTDO-SWO
PB4.Mode=Full_Duplex_Master
PB4.Signal=SPI3_MISO
PB5.Mode=Full_Duplex_Master
PB5.Signal=SPI3_MOSI
PB6.GPIOParameters=GPIO_Label
PB6.GPIO_Label=LoRaDIO0
PB6.Signal=GPXTI6
PB7.GPIOParameters=GPIO_Label
PB7.GPIO_Label=LoRaDIO2
PB7.Signal=GPIO_Input
PC0.GPIOParameters=PinState,GPIO_Label
PC0.GPIO_Label=CSFlashmMemory
PC0.PinState=GPIO_PIN_SET
PC0.Signal=GPIO_Output
PC1.GPIOParameters=PinState,GPIO_Label
PC1.GPIO_Label=CS_SD_Card
PC1.PinState=GPIO_PIN_SET
PC1.Signal=GPIO_Output
PC10.Mode=Full_Duplex_Master
PC10.Signal=SPI3_SCK
PC11.Mode=Asynchronous
PC11.Signal=UART4_RX
PC12.Mode=Asynchronous
PC12.Signal=UART5_TX
PC2.Mode=Full_Duplex_Master
PC2.Signal=SPI2_MISO
PC3.Signal=ADCx_IN13
PC4.GPIOParameters=GPIO_Label
PC4.GPIO_Label=BuzzerControl
PC4.Signal=GPIO_Output
PC5.Signal=ADCx_IN15
PC6.GPIOParameters=PinState,GPIO_Label
PC6.GPIO_Label=DrogueIgnite
PC6.PinState=GPIO_PIN_RESET
PC6.Signal=GPIO_Output
PC7.GPIOParameters=PinState,GPIO_Label
PC7.GPIO_Label=CSBarometer
PC7.PinState=GPIO_PIN_SET
PC7.Signal=GPIO_Output
PC9.GPIOParameters=GPIO_Label
PC9.GPIO_Label=GPS2ResetPin
PC9.Signal=GPIO_Output
PD2.Mode=Asynchronous
PD2.Signal=UART5_RX
PH0-OSC_IN.Mode=HSE-External-Oscillator
PH0-OSC_IN.Signal=RCC_OSC_IN
PH1-OSC_OUT.Mode=HSE-External-Oscillator
PH1-OSC_OUT.Signal=RCC_OSC_OUT
RCC.HSE_VALUE=8000000
RCC.SYSCLKFreq_VALUE=72000000
RCC.SYSCLKSource=RCC_SYSCLKSOURCE_PLLCLK
board=custom
